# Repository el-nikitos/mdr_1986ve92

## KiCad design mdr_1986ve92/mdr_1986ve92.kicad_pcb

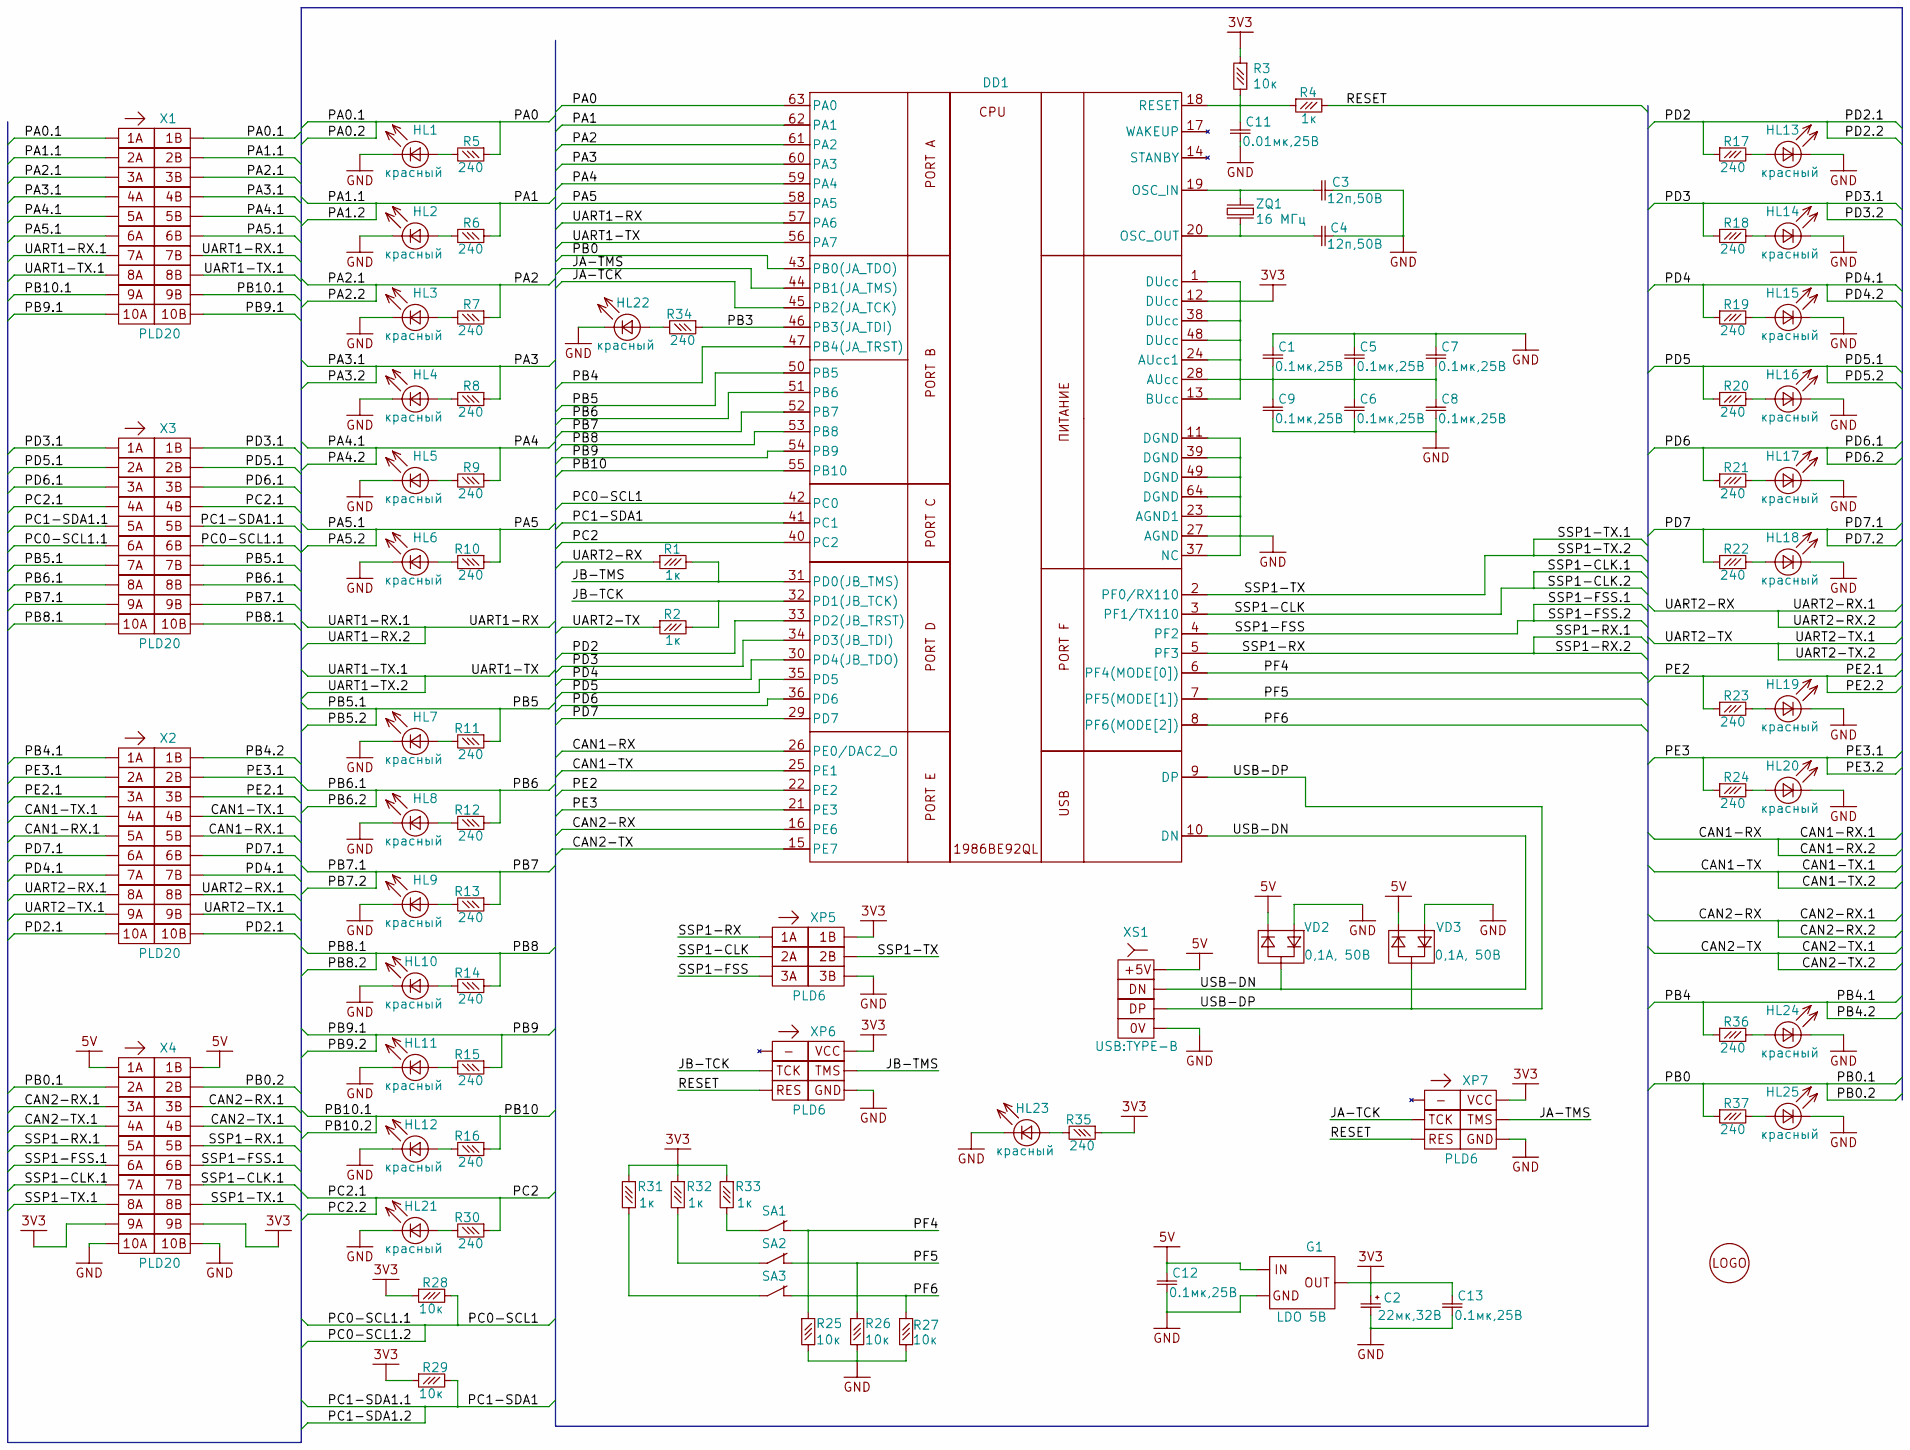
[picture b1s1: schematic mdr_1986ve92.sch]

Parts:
C1, C5, C6, C7, C8, C9, C12, C13: smd-конденсатор-керамика*0,1мк*25В*0805*ВП; Конденсатор_SMD_IEC_0805
C2: smd-конденсатор-тантал*22мк*32В*E*ВП; Конденсатор_тантал_SMD_m7343
C3, C4: smd-конденсатор-керамика*12п*50В*0603*ВП; Конденсатор_SMD_IEC_0603
C11: smd-конденсатор-керамика*0,1мк*25В*0805*ВП; Конденсатор_SMD_IEC_0603
DD1: Микросхема_интегральная*1986ВЕ92QL; Микросхема_1986ВЕ92QL
G1: Микросхема*LDO*IN30V*OUT5V*0.5A*КТ-89*ОТК; Корпус_КТ-89
HL1, HL2, HL3, HL4, HL5, HL6, HL7, HL8, HL9, HL10, HL11, HL12, HL13, HL14, HL15, HL16, HL17, HL18, HL19, HL20, HL21, HL22, HL23, HL24, HL25: smd-светодиод*красный*10мА*0603*ВП; Светодиод_SMD_IEC_0603(AK)
R1, R2, R4: smd-резистор*1к*0603*ВП; Резистор_SMD_IEC_0603-0,075_Вт
R3, R28, R29, R31, R32, R33: smd-резистор*10к*0603*ВП; Резистор_SMD_IEC_0603-0,075_Вт
R5, R6, R7, R8, R9, R10, R11, R12, R13, R14, R15, R16, R17, R18, R19, R20, R21, R22, R23, R24, R25, R26, R27, R30, R34, R35, R36, R37: smd-резистор*240*0603*ВП; Резистор_SMD_IEC_0603-0,075_Вт
SA1, SA2, SA3: Переключатель*DIP*вертикальный*2,5мм; переключатель_движковый_2,5мм_1канал
VD2, VD3: smd-диод-двухнаправленный*0,1А*50В*SOT-23*ВП; Корпус_КТ-46
X1, X2, X3, X4: Вилка*PLD*20контактов*2ряда*вертикальная; Вилка_СНП346-10ВП21-2-вверх
X5: ico*logo*el-nikitos*10x10; nikitos_10x10
XP5: Вилка*PLD*6контактов*2ряда*вертикальная; Вилка_SNP346-6VP21-2
XP6, XP7: Вилка*PLD*6контактов*2ряда*вертикальная*SWD; Вилка_SNP346-6VP21-2
XS1: Розетка*USB-TYPE-B*ВП; Розетка_СП424-4РП(USB)
ZQ1: Резонатор*16МГЦ*HC49S*ВП&1; Резонатор_РК456МДУ(DIP)

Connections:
3V3: C1.2, C2.1, C5.2, C6.1, C7.2, C8.1, C9.1, C13.1, DD1.1 (DUcc), DD1.12 (DUcc), DD1.13 (BUcc), DD1.24 (AUcc1), DD1.28 (AUcc), DD1.38 (DUcc), DD1.48 (DUcc), G1.3 (Uo), R3.1, R28.1, R29.1, R31.1, R32.1, R33.1, R35.1, X4.9A, X4.9B, XP5.1B, XP6.1B, XP7.1B
5V: C12.1, G1.1 (Ui), VD2.2 (K2), VD3.2 (K2), X4.1A, X4.1B, XS1.1
/CAN1-RX: DD1.26 (PE0/DAC2_O), X2.5A, X2.5B
/CAN1-TX: DD1.25 (PE1), X2.4A, X2.4B
/CAN2-RX: DD1.16 (PE6), X4.3A, X4.3B
/CAN2-TX: DD1.15 (PE7), X4.4A, X4.4B
/JA-TCK: DD1.45 (PB2(JA_TCK)), XP7.2A
/JA-TMS: DD1.44 (PB1(JA_TMS)), XP7.2B
/JB-TCK: DD1.32 (PD1(JB_TCK)), R2.2, XP6.2A
/JB-TMS: DD1.31 (PD0(JB_TMS)), R1.2, XP6.2B
/PA0: DD1.63 (PA0), R5.1, X1.1A, X1.1B
/PA1: DD1.62 (PA1), R6.1, X1.2A, X1.2B
/PA2: DD1.61 (PA2), R7.1, X1.3A, X1.3B
/PA3: DD1.60 (PA3), R8.1, X1.4A, X1.4B
/PA4: DD1.59 (PA4), R9.1, X1.5A, X1.5B
/PA5: DD1.58 (PA5), R10.1, X1.6A, X1.6B
/PB0: DD1.43 (PB0(JA_TDO)), R37.1, X4.2A, X4.2B
/PB3: DD1.46 (PB3(JA_TDI)), R34.1
/PB4: DD1.47 (PB4(JA_TRST)), R36.1, X2.1A, X2.1B
/PB5: DD1.50 (PB5), R11.1, X3.7A, X3.7B
/PB6: DD1.51 (PB6), R12.1, X3.8A, X3.8B
/PB7: DD1.52 (PB7), R13.1, X3.9A, X3.9B
/PB8: DD1.53 (PB8), R14.1, X3.10A, X3.10B
/PB9: DD1.54 (PB9), R15.1, X1.10A, X1.10B
/PB10: DD1.55 (PB10), R16.1, X1.9A, X1.9B
/PC0-SCL1: DD1.42 (PC0), R28.2, X3.6A, X3.6B
/PC1-SDA1: DD1.41 (PC1), R29.2, X3.5A, X3.5B
/PC2: DD1.40 (PC2), R30.1, X3.4A, X3.4B
/PD2: DD1.33 (PD2(JB_TRST)), R17.1, X2.10A, X2.10B
/PD3: DD1.34 (PD3(JB_TDI)), R18.1, X3.1A, X3.1B
/PD4: DD1.30 (PD4(JB_TDO)), R19.1, X2.7A, X2.7B
/PD5: DD1.35 (PD5), R20.1, X3.2A, X3.2B
/PD6: DD1.36 (PD6), R21.1, X3.3A, X3.3B
/PD7: DD1.29 (PD7), R22.1, X2.6A, X2.6B
/PE2: DD1.22 (PE2), R23.1, X2.3A, X2.3B
/PE3: DD1.21 (PE3), R24.1, X2.2A, X2.2B
/PF4: DD1.6 (PF4(MODE[0])), R25.1, SA1.2
/PF5: DD1.7 (PF5(MODE[1])), R26.1, SA2.2
/PF6: DD1.8 (PF6(MODE[2])), R27.2, SA3.2
/RESET: R4.2, XP6.3A, XP7.3A
/SSP1-CLK: DD1.3 (PF1/TX110), X4.7A, X4.7B, XP5.2A
/SSP1-FSS: DD1.4 (PF2), X4.6A, X4.6B, XP5.3A
/SSP1-RX: DD1.5 (PF3), X4.5A, X4.5B, XP5.1A
/SSP1-TX: DD1.2 (PF0/RX110), X4.8A, X4.8B, XP5.2B
/UART1-RX: DD1.57 (PA6), X1.7A, X1.7B
/UART1-TX: DD1.56 (PA7), X1.8A, X1.8B
/UART2-RX: R1.1, X2.8A, X2.8B
/UART2-TX: R2.1, X2.9A, X2.9B
/USB-DN: DD1.10 (DN), VD2.3 (K1), XS1.2
/USB-DP: DD1.9 (DP), VD3.3 (K1), XS1.3
GND: C1.1, C2.2, C3.2, C4.2, C5.1, C6.2, C7.1, C8.2, C9.2, C11.2, C12.2, C13.2, DD1.11 (DGND), DD1.23 (AGND1), DD1.27 (AGND), DD1.37 (NC), DD1.39 (DGND), DD1.49 (DGND), DD1.64 (DGND), G1.4 (GND), HL1.K, HL2.K, HL3.K, HL4.K, HL5.K, HL6.K, HL7.K, HL8.K, HL9.K, HL10.K, HL11.K, HL12.K, HL13.K, HL14.K, HL15.K, HL16.K, HL17.K, HL18.K, HL19.K, HL20.K, HL21.K, HL22.K, HL23.K, HL24.K, HL25.K, R25.2, R26.2, R27.1, VD2.1 (A1), VD3.1 (A1), X4.10A, X4.10B, XP5.3B, XP6.3B, XP7.3B, XS1.4
unnamed: C3.1, DD1.19 (OSC_IN), ZQ1.1
unnamed: C4.1, DD1.20 (OSC_OUT), ZQ1.2
unnamed: C11.1, DD1.18 (RESET), R3.2, R4.1
unnamed: HL1.A, R5.2
unnamed: HL2.A, R6.2
unnamed: HL3.A, R7.2
unnamed: HL4.A, R8.2
unnamed: HL5.A, R9.2
unnamed: HL6.A, R10.2
unnamed: HL7.A, R11.2
unnamed: HL8.A, R12.2
unnamed: HL9.A, R13.2
unnamed: HL10.A, R14.2
unnamed: HL11.A, R15.2
unnamed: HL12.A, R16.2
unnamed: HL13.A, R17.2
unnamed: HL14.A, R18.2
unnamed: HL15.A, R19.2
unnamed: HL16.A, R20.2
unnamed: HL17.A, R21.2
unnamed: HL18.A, R22.2
unnamed: HL19.A, R23.2
unnamed: HL20.A, R24.2
unnamed: HL21.A, R30.2
unnamed: HL22.A, R34.2
unnamed: HL23.A, R35.2
unnamed: HL24.A, R36.2
unnamed: HL25.A, R37.2
unnamed: R31.2, SA3.1
unnamed: R32.2, SA2.1
unnamed: R33.2, SA1.1

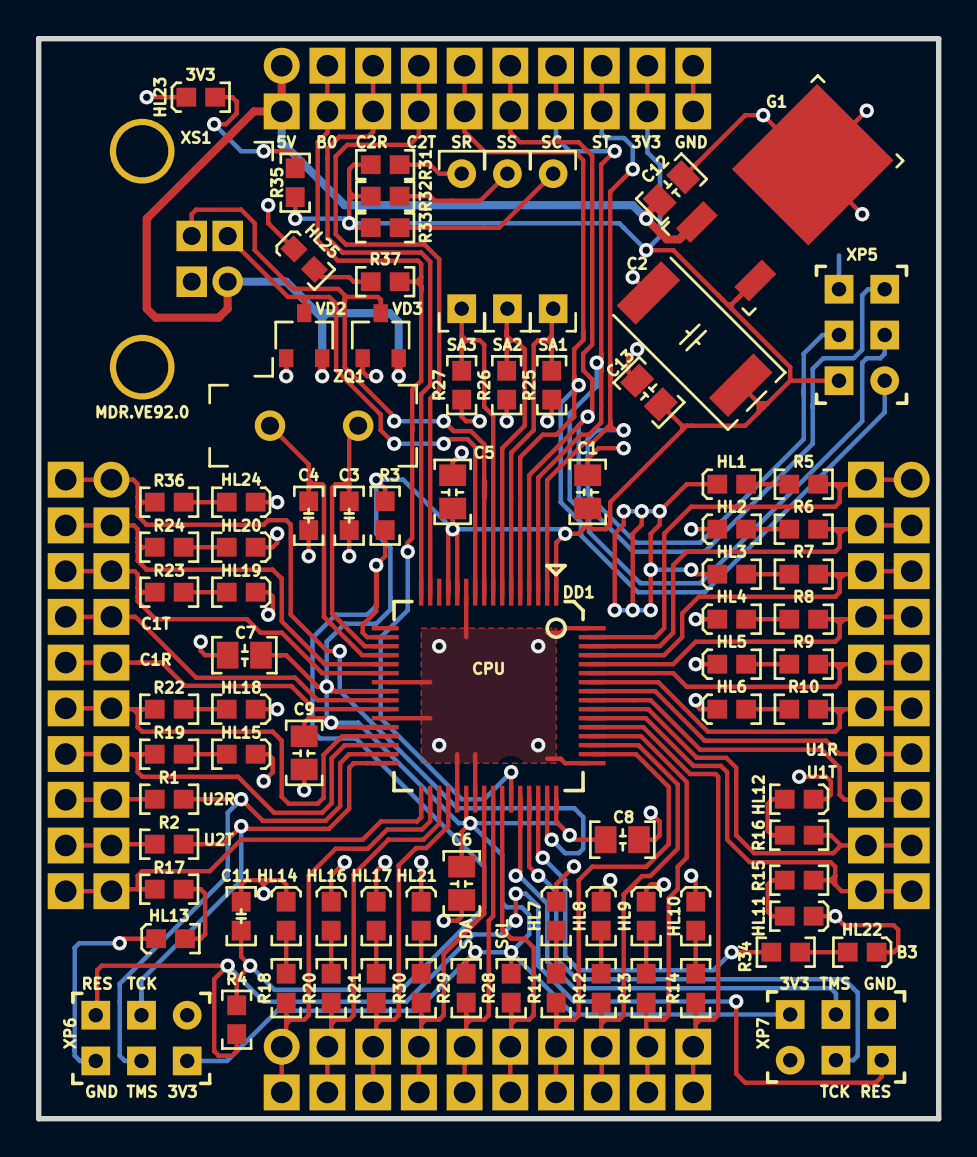
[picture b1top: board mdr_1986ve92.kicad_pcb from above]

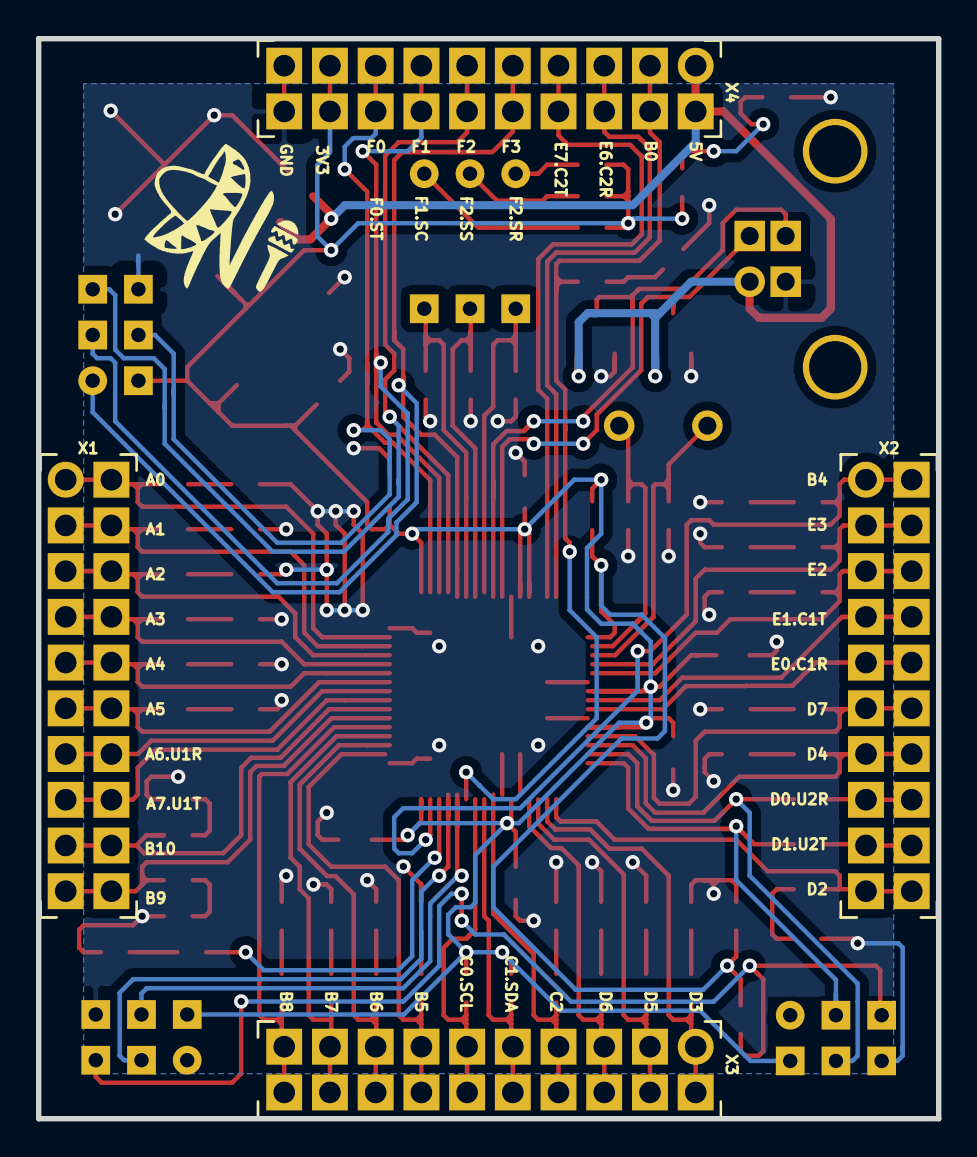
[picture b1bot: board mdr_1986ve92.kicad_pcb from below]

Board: 2 copper layers, 50.0 x 60.0 mm, 91 parts (5 on the bottom side), 82 nets.

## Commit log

2022-02-20 процессорный модуль на базе ВЕ92QL
